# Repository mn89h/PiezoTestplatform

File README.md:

# Custom ASIC Test PCB for Ultrasonic Communication

This project involves the design and development of a custom printed circuit board (PCB) for testing an Application-Specific Integrated Circuit (ASIC) used in ultrasonic communication. The goal is to enable two-way ultrasonic communication with energy harvesting capabilities. This was developed as part of a project seminar in the Integrated Electronic Systems (IES) lab at the Technical University of Darmstadt.

Features:

    Ultrasonic Transmission and Reception: Supports two-way communication using piezoelectric transducers for transmitting and receiving ultrasonic waves.
    Custom PCB Design: Designed a custom PCB including components like a piezo driver, analog-to-digital converter (ADC), comparator, and FPGA for signal processing.
    Energy Harvesting: Capable of using wireless power harvesting techniques for communication where battery power is not feasible.
    FPGA Control: The system is controlled by a Xilinx Spartan-7 FPGA, with signal processing logic implemented in Verilog.

## System Overview

The system consists of both hardware and software platforms:

    Hardware: Includes a piezo driver stage, input amplifier, ADC, comparator, and FPGA. The PCB was designed using KiCAD 6.0.
    Software: Implemented in Verilog for the Xilinx Spartan-7 FPGA, handling communication, data transfer, and signal processing.

## Project Structure

    Piezo_DevBoard: A two-layer PCB designed for high-frequency ultrasonic communication with minimal noise and optimal power management.
    Piezo_TestPlatform: The FPGA core handles the communication between the FPGA and external systems through serial interfaces and processes data from the piezo transducers. Python code for interpreting incoming data is provided in the misc folder.

## Detailed Overview

Please refer to the [report](Report/main.pdf) and [presentation](Presentation/Präsentation.pdf) for a more in-depth look.

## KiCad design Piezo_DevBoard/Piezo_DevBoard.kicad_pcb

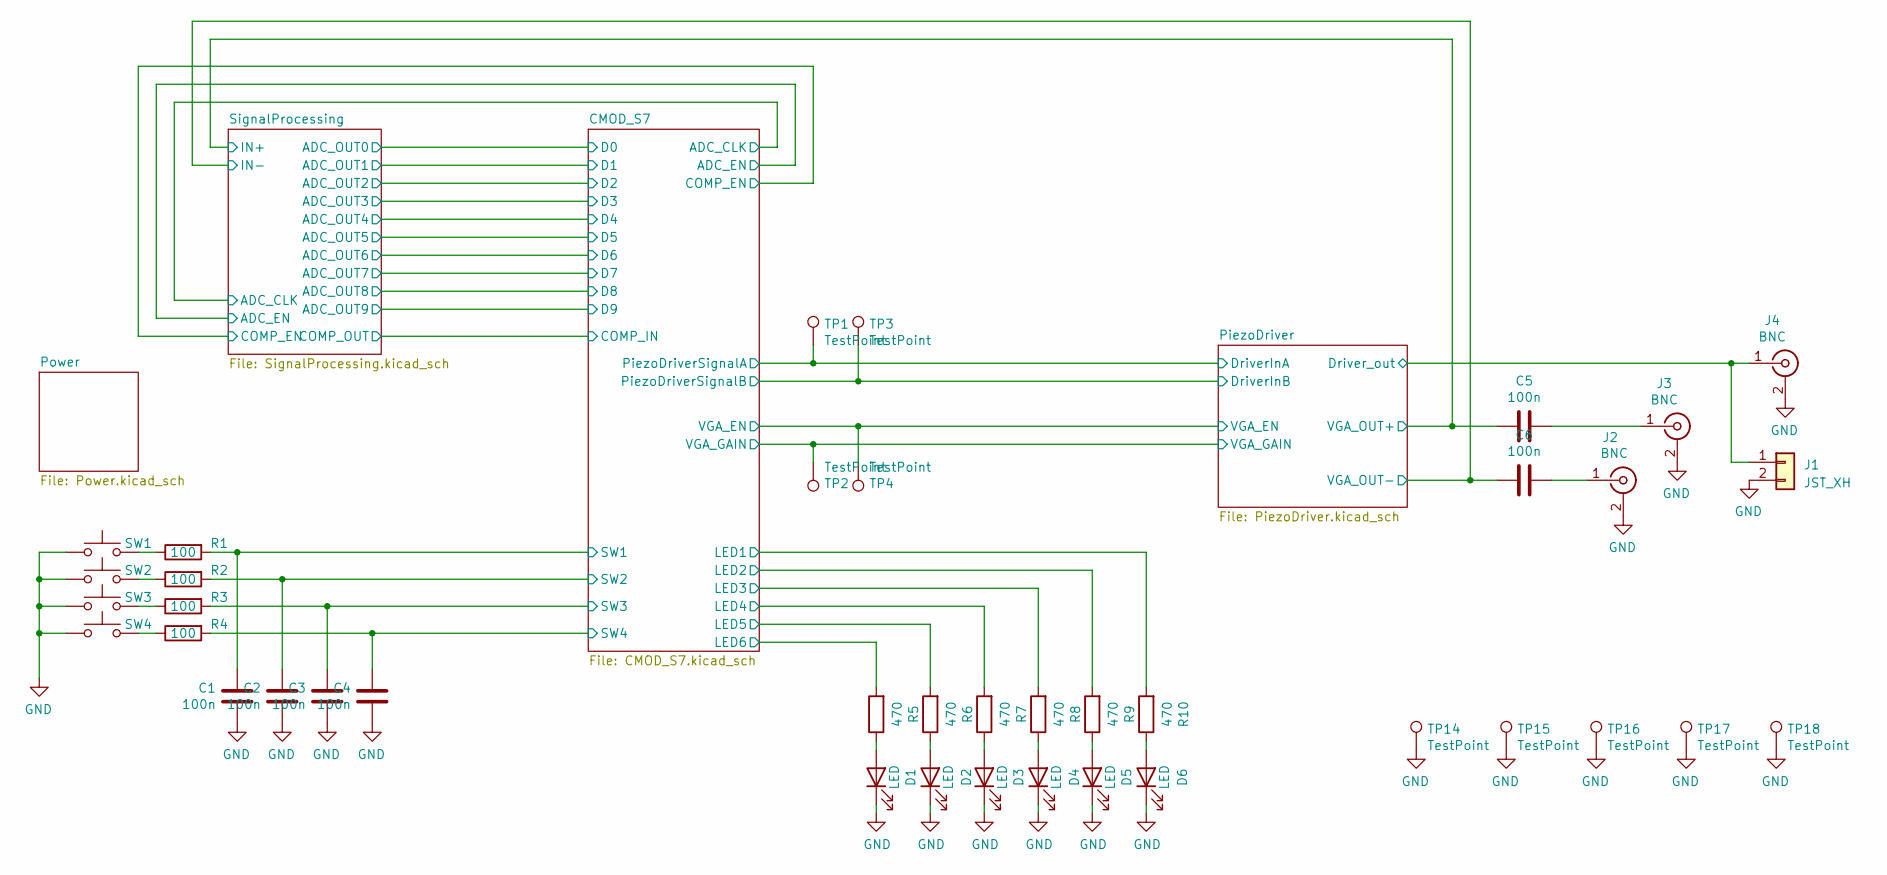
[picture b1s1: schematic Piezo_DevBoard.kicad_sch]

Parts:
C1, C2, C3, C4, C5, C6: 100n; C_0603_1608Metric_Pad1.08x0.95mm_HandSolder
D1, D2, D3, D4, D5, D6: LED; LED_0805_2012Metric_Pad1.15x1.40mm_HandSolder
J1: JST_XH; JST_XH_B2B-XH-A_1x02_P2.50mm_Vertical
J2, J3, J4: BNC; BNC_Amphenol_B6252HB-NPP3G-50_Horizontal
R1, R2, R3, R4: 100; R_0603_1608Metric_Pad0.98x0.95mm_HandSolder
R5, R6, R7, R8, R9, R10: 470; R_0603_1608Metric_Pad0.98x0.95mm_HandSolder
SW1, SW2, SW3, SW4: SW_Push; SW_Push_1P1T_NO_6x6mm_H9.5mm
TP1, TP2, TP3, TP4, TP14, TP15, TP16, TP17, TP18: TestPoint; TestPoint_Loop_D1.80mm_Drill1.0mm_Beaded

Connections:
/CMOD_S7/LED1: R10.2; also elsewhere on the board
/CMOD_S7/LED2: R9.2; also elsewhere on the board
/CMOD_S7/LED3: R8.2; also elsewhere on the board
/CMOD_S7/LED4: R7.2; also elsewhere on the board
/CMOD_S7/LED5: R6.2; also elsewhere on the board
/CMOD_S7/LED6: R5.2; also elsewhere on the board
/CMOD_S7/PiezoDriverSignalA: TP1.1; also elsewhere on the board
/CMOD_S7/PiezoDriverSignalB: TP3.1; also elsewhere on the board
/CMOD_S7/SW1: C1.1, R1.2; also elsewhere on the board
/CMOD_S7/SW2: C2.1, R2.2; also elsewhere on the board
/CMOD_S7/SW3: C3.1, R3.2; also elsewhere on the board
/CMOD_S7/SW4: C4.1, R4.2; also elsewhere on the board
/CMOD_S7/VGA_EN: TP4.1; also elsewhere on the board
/CMOD_S7/VGA_GAIN: TP2.1; also elsewhere on the board
/PiezoDriver/Driver_out: J1.1, J4.1 (In); also elsewhere on the board
/PiezoDriver/VGA_OUT+: C5.2; also elsewhere on the board
/PiezoDriver/VGA_OUT-: C6.2; also elsewhere on the board
GND: C1.2, C2.2, C3.2, C4.2, D1.1 (K), D2.1 (K), D3.1 (K), D4.1 (K), D5.1 (K), D6.1 (K), J1.2, J2.2 (Ext), J3.2 (Ext), J4.2 (Ext), SW1.2, SW2.2, SW3.2, SW4.2, TP14.1, TP15.1, TP16.1, TP17.1, TP18.1; also elsewhere on the board
unnamed: C5.1, J3.1 (In)
unnamed: C6.1, J2.1 (In)
unnamed: D1.2 (A), R5.1
unnamed: D2.2 (A), R6.1
unnamed: D3.2 (A), R7.1
unnamed: D4.2 (A), R8.1
unnamed: D5.2 (A), R9.1
unnamed: D6.2 (A), R10.1
unnamed: R1.1, SW1.1
unnamed: R2.1, SW2.1
unnamed: R3.1, SW3.1
unnamed: R4.1, SW4.1

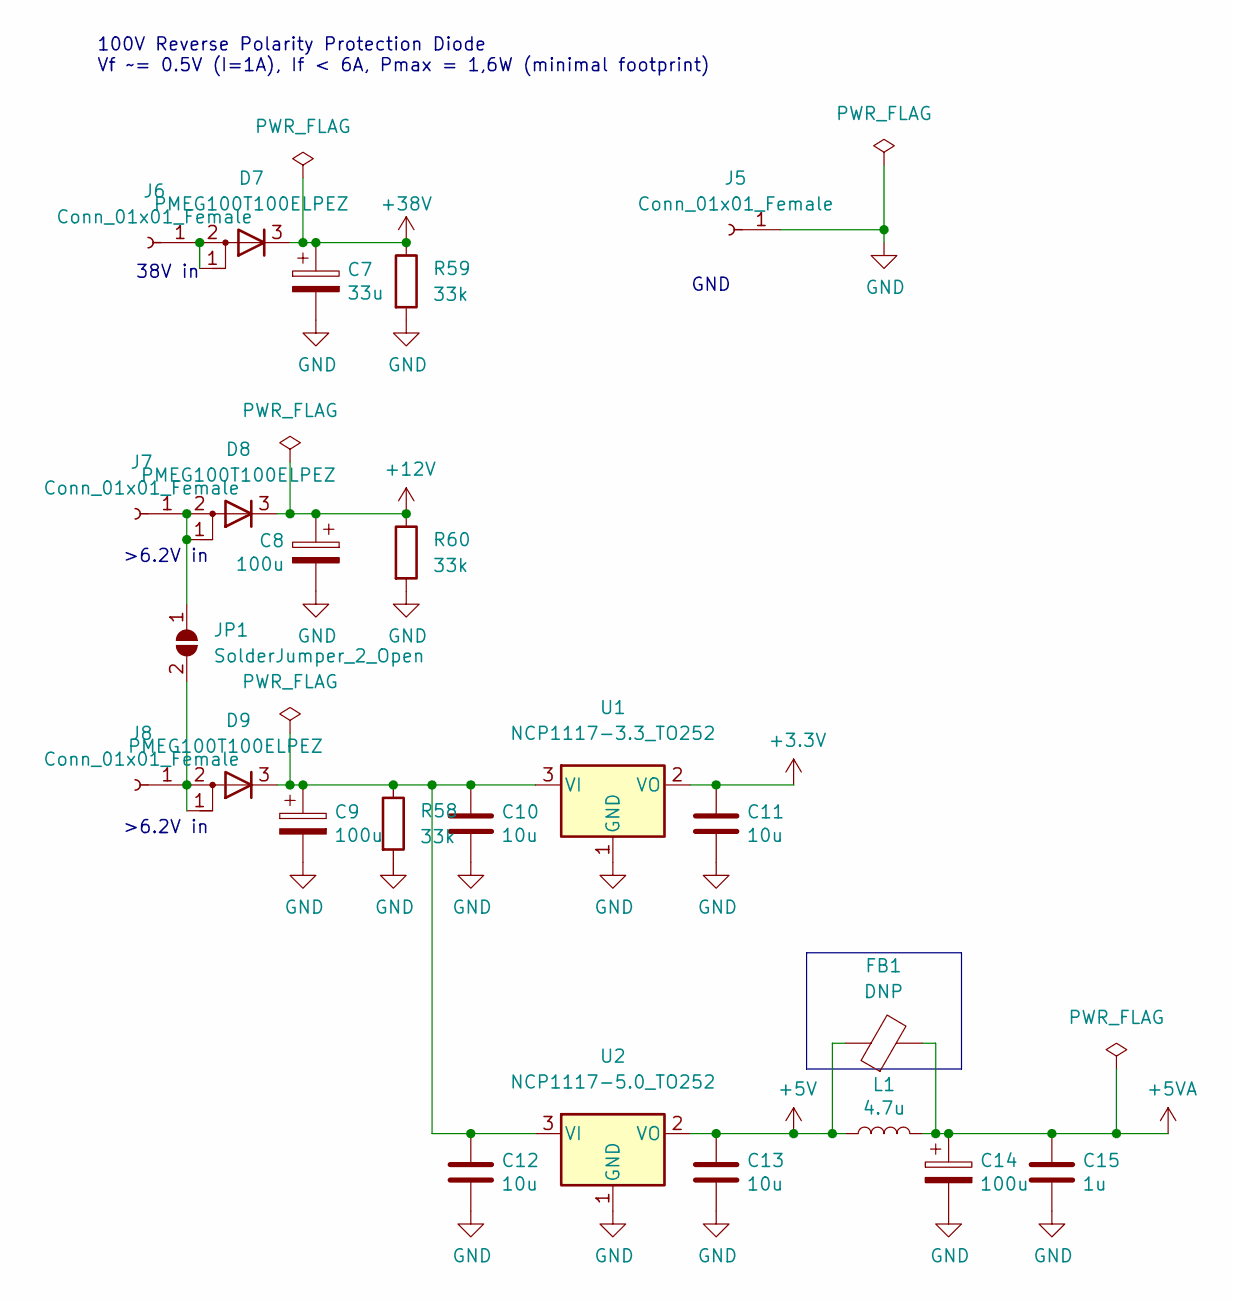
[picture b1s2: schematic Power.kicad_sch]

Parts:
C7: 33u; CP_Elec_10x10.5
C8, C9, C14: 100u; CP_Elec_6.3x7.7
C10, C11, C12, C13: 10u; C_0805_2012Metric_Pad1.18x1.45mm_HandSolder
C15: 1u; C_0603_1608Metric_Pad1.08x0.95mm_HandSolder
D7, D8, D9: PMEG100T100ELPEZ; Nexperia_CFP15_SOT-1289
FB1: DNP; L_0603_1608Metric_Pad1.05x0.95mm_HandSolder
J5, J6, J7, J8: Conn_01x01_Female; BananaJack_24.243
JP1: SolderJumper_2_Open; SolderJumper-2_P1.3mm_Open_TrianglePad1.0x1.5mm
L1: 4.7u; L_Wuerth_MAPI-4030
R58, R59, R60: 33k; R_1206_3216Metric_Pad1.30x1.75mm_HandSolder
U1: NCP1117-3.3_TO252; TO-252-2
U2: NCP1117-5.0_TO252; TO-252-2

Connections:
+3.3V: C11.1, U1.2 (VO); also elsewhere on the board
+5V: C13.1, FB1.1, L1.1, U2.2 (VO); also elsewhere on the board
+5VA: C14.1, C15.1, FB1.2, L1.2; also elsewhere on the board
+12V: C8.1, D8.3 (K), R60.1; also elsewhere on the board
+38V: C7.1, D7.3 (K), R59.1; also elsewhere on the board
GND: C7.2, C8.2, C9.2, C10.2, C11.2, C12.2, C13.2, C14.2, C15.2, J5.1, R58.2, R59.2, R60.2, U1.1 (GND), U2.1 (GND); also elsewhere on the board
unnamed: C9.1, C10.1, C12.1, D9.3 (K), R58.1, U1.3 (VI), U2.3 (VI)
unnamed: D7.1 (A), D7.2 (A), J6.1
unnamed: D8.1 (A), D8.2 (A), J7.1, JP1.1 (A)
unnamed: D9.1 (A), D9.2 (A), J8.1, JP1.2 (B)

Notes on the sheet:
38V in
>6.2V in
GND
100V Reverse Polarity Protection Diode Vf ~= 0.5V (I=1A), If < 6A, Pmax = 1,6W (minimal footprint)

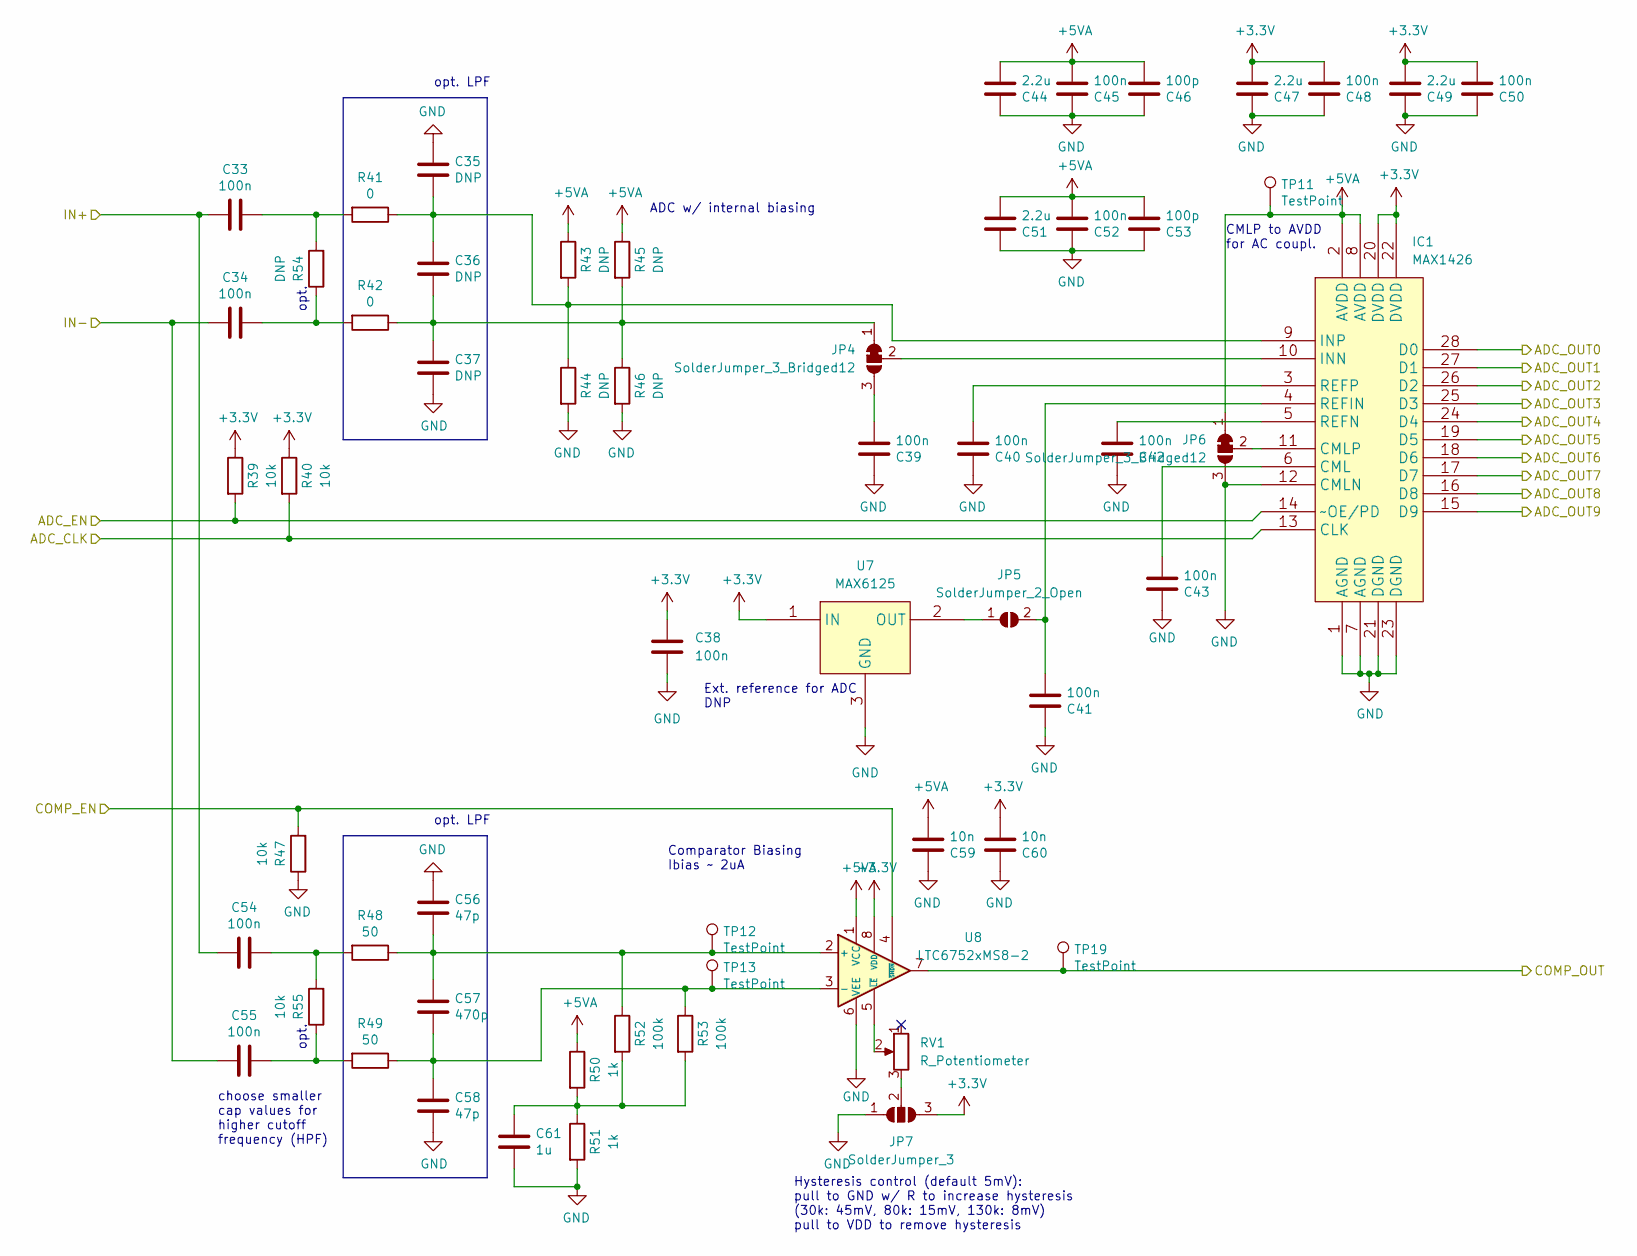
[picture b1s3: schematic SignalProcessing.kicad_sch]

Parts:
C33, C34, C38, C39, C40, C41, C42, C43, C45, C48, C50, C52, C54, C55: 100n; C_0603_1608Metric_Pad1.08x0.95mm_HandSolder
C35, C36, C37: DNP; C_0603_1608Metric_Pad1.08x0.95mm_HandSolder
C44, C47, C49, C51: 2.2u; C_0603_1608Metric_Pad1.08x0.95mm_HandSolder
C46, C53: 100p; C_0603_1608Metric_Pad1.08x0.95mm_HandSolder
C56, C58: 47p; C_0603_1608Metric_Pad1.08x0.95mm_HandSolder
C57: 470p; C_0603_1608Metric_Pad1.08x0.95mm_HandSolder
C59, C60: 10n; C_0603_1608Metric_Pad1.08x0.95mm_HandSolder
C61: 1u; C_0603_1608Metric_Pad1.08x0.95mm_HandSolder
IC1: MAX1426; SSOP-28_5.3x10.2mm_P0.65mm
JP4, JP6: SolderJumper_3_Bridged12; SolderJumper-3_P1.3mm_Bridged12_RoundedPad1.0x1.5mm
JP5: SolderJumper_2_Open; SolderJumper-2_P1.3mm_Open_RoundedPad1.0x1.5mm
JP7: SolderJumper_3; SolderJumper-3_P1.3mm_Open_RoundedPad1.0x1.5mm
R39, R40, R47, R55: 10k; R_0603_1608Metric_Pad0.98x0.95mm_HandSolder
R41, R42: 0; R_0603_1608Metric_Pad0.98x0.95mm_HandSolder
R43, R44, R45, R46, R54: DNP; R_0603_1608Metric_Pad0.98x0.95mm_HandSolder
R48, R49: 50; R_0603_1608Metric_Pad0.98x0.95mm_HandSolder
R50, R51: 1k; R_0603_1608Metric_Pad0.98x0.95mm_HandSolder
R52, R53: 100k; R_0603_1608Metric_Pad0.98x0.95mm_HandSolder
RV1: R_Potentiometer; Potentiometer_Bourns_3009P_Horizontal
TP11, TP12, TP13, TP19: TestPoint; TestPoint_Loop_D1.80mm_Drill1.0mm_Beaded
U7: MAX6125; SOT-23
U8: LTC6752xMS8-2; MSOP-8_3x3mm_P0.65mm

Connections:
+3.3V: C38.1, C47.2, C48.2, C49.2, C50.2, C60.2, IC1.20 (DVDD), IC1.22 (DVDD), JP7.3 (B), R39.1, R40.1, U7.1 (IN), U8.8 (VDD); also elsewhere on the board
+5VA: C44.2, C45.2, C46.2, C51.2, C52.2, C53.2, C59.2, IC1.2 (AVDD), IC1.8 (AVDD), JP6.1 (A), R43.1, R45.1, R50.1, TP11.1, U8.1 (VCC); also elsewhere on the board
/CMOD_S7/ADC_CLK: IC1.13 (CLK), R40.2; also elsewhere on the board
/CMOD_S7/ADC_EN: IC1.14 (~OE/PD), R39.2; also elsewhere on the board
/CMOD_S7/COMP_EN: R47.2, U8.4 (~SHDN); also elsewhere on the board
/CMOD_S7/COMP_IN: TP19.1, U8.7; also elsewhere on the board
/CMOD_S7/D0: IC1.28 (D0); also elsewhere on the board
/CMOD_S7/D1: IC1.27 (D1); also elsewhere on the board
/CMOD_S7/D2: IC1.26 (D2); also elsewhere on the board
/CMOD_S7/D3: IC1.25 (D3); also elsewhere on the board
/CMOD_S7/D4: IC1.24 (D4); also elsewhere on the board
/CMOD_S7/D5: IC1.19 (D5); also elsewhere on the board
/CMOD_S7/D6: IC1.18 (D6); also elsewhere on the board
/CMOD_S7/D7: IC1.17 (D7); also elsewhere on the board
/CMOD_S7/D8: IC1.16 (D8); also elsewhere on the board
/CMOD_S7/D9: IC1.15 (D9); also elsewhere on the board
/PiezoDriver/VGA_OUT+: C33.2, C54.2; also elsewhere on the board
/PiezoDriver/VGA_OUT-: C34.2, C55.2; also elsewhere on the board
GND: C35.1, C37.2, C38.2, C39.1, C40.1, C41.1, C42.1, C43.1, C44.1, C45.1, C46.1, C47.1, C48.1, C49.1, C50.1, C51.1, C52.1, C53.1, C56.1, C58.2, C59.1, C60.1, C61.2, IC1.1 (AGND), IC1.7 (AGND), IC1.12 (CMLN), IC1.21 (DGND), IC1.23 (DGND), JP6.3 (B), JP7.1 (A), R44.2, R46.2, R47.1, R51.2, U7.3 (GND), U8.6 (VEE); also elsewhere on the board
unnamed: C33.1, R41.2, R54.2
unnamed: C34.1, R42.2, R54.1
unnamed: C35.2, C36.1, IC1.9 (INP), R41.1, R43.2, R44.1
unnamed: C36.2, C37.1, JP4.1 (A), R42.1, R45.2, R46.1
unnamed: C39.2, JP4.3 (B)
unnamed: C40.2, IC1.3 (REFP)
unnamed: C41.2, IC1.4 (REFIN), JP5.2 (B)
unnamed: C42.2, IC1.5 (REFN)
unnamed: C43.2, IC1.6 (CML)
unnamed: C54.1, R48.2, R55.2
unnamed: C55.1, R49.2, R55.1
unnamed: C56.2, C57.1, R48.1, R52.1, TP12.1, U8.2 (+)
unnamed: C57.2, C58.1, R49.1, R53.1, TP13.1, U8.3 (-)
unnamed: C61.1, R50.2, R51.1, R52.2, R53.2
unnamed: IC1.10 (INN), JP4.2 (C)
unnamed: IC1.11 (CMLP), JP6.2 (C)
unnamed: JP5.1 (A), U7.2 (OUT)
unnamed: JP7.2 (C), RV1.3
unnamed: RV1.2, U8.5 (~LE)

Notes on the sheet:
opt. LPF
ADC w/ internal biasing
CMLP to AVDD for AC coupl.
opt.
Ext. reference for ADC DNP
Hysteresis control (default 5mV): pull to GND w/ R to increase hysteresis (30k: 45mV, 80k: 15mV, 130k: 8mV) pull to VDD to remove hysteresis
choose smaller cap values for higher cutoff frequency (HPF)
Comparator Biasing Ibias ~ 2uA

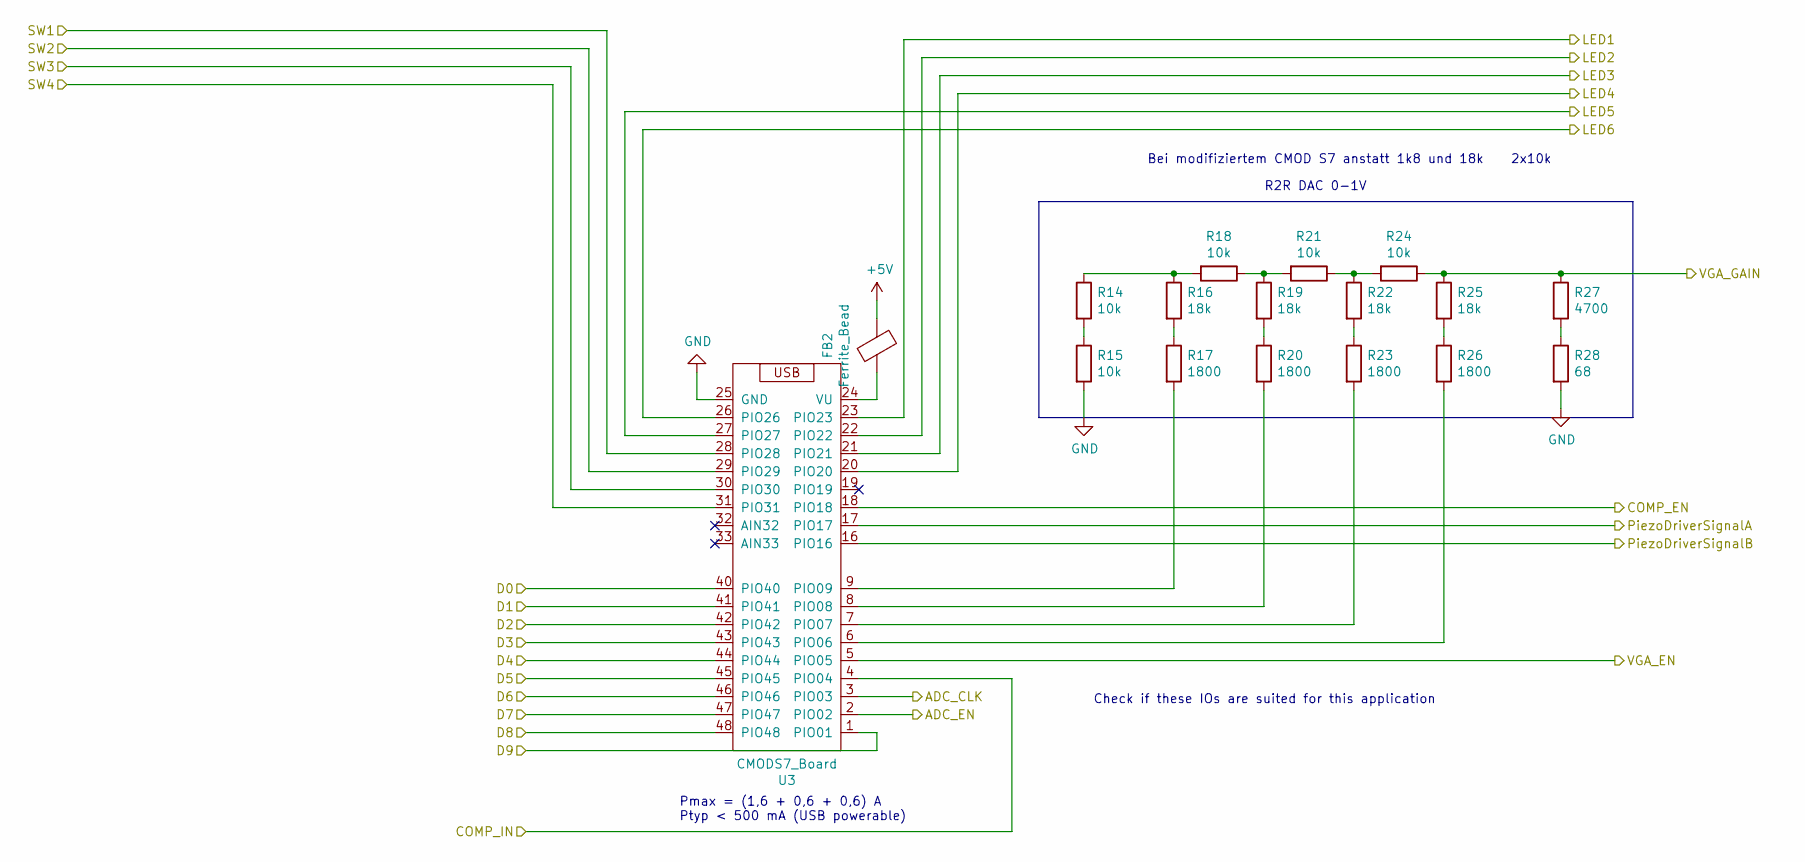
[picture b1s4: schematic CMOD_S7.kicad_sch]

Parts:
FB2: Ferrite_Bead; L_0603_1608Metric_Pad1.05x0.95mm_HandSolder
R14, R15, R18, R21, R24: 10k; R_0603_1608Metric_Pad0.98x0.95mm_HandSolder
R16, R19, R22, R25: 18k; R_0603_1608Metric_Pad0.98x0.95mm_HandSolder
R17, R20, R23, R26: 1800; R_0603_1608Metric_Pad0.98x0.95mm_HandSolder
R27: 4700; R_0603_1608Metric_Pad0.98x0.95mm_HandSolder
R28: 68; R_0603_1608Metric_Pad0.98x0.95mm_HandSolder
U3: CMODS7_Board; CMOD_S7_Socket

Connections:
+5V: FB2.2; also elsewhere on the board
/CMOD_S7/ADC_CLK: U3.3 (PIO03); also elsewhere on the board
/CMOD_S7/ADC_EN: U3.2 (PIO02); also elsewhere on the board
/CMOD_S7/COMP_EN: U3.18 (PIO18); also elsewhere on the board
/CMOD_S7/COMP_IN: U3.4 (PIO04); also elsewhere on the board
/CMOD_S7/D0: U3.40 (PIO40); also elsewhere on the board
/CMOD_S7/D1: U3.41 (PIO41); also elsewhere on the board
/CMOD_S7/D2: U3.42 (PIO42); also elsewhere on the board
/CMOD_S7/D3: U3.43 (PIO43); also elsewhere on the board
/CMOD_S7/D4: U3.44 (PIO44); also elsewhere on the board
/CMOD_S7/D5: U3.45 (PIO45); also elsewhere on the board
/CMOD_S7/D6: U3.46 (PIO46); also elsewhere on the board
/CMOD_S7/D7: U3.47 (PIO47); also elsewhere on the board
/CMOD_S7/D8: U3.48 (PIO48); also elsewhere on the board
/CMOD_S7/D9: U3.1 (PIO01); also elsewhere on the board
/CMOD_S7/LED1: U3.23 (PIO23); also elsewhere on the board
/CMOD_S7/LED2: U3.22 (PIO22); also elsewhere on the board
/CMOD_S7/LED3: U3.21 (PIO21); also elsewhere on the board
/CMOD_S7/LED4: U3.20 (PIO20); also elsewhere on the board
/CMOD_S7/LED5: U3.27 (PIO27); also elsewhere on the board
/CMOD_S7/LED6: U3.26 (PIO26); also elsewhere on the board
/CMOD_S7/PiezoDriverSignalA: U3.17 (PIO17); also elsewhere on the board
/CMOD_S7/PiezoDriverSignalB: U3.16 (PIO16); also elsewhere on the board
/CMOD_S7/SW1: U3.28 (PIO28); also elsewhere on the board
/CMOD_S7/SW2: U3.29 (PIO29); also elsewhere on the board
/CMOD_S7/SW3: U3.30 (PIO30); also elsewhere on the board
/CMOD_S7/SW4: U3.31 (PIO31); also elsewhere on the board
/CMOD_S7/VGA_EN: U3.5 (PIO05); also elsewhere on the board
/CMOD_S7/VGA_GAIN: R24.1, R25.1, R27.1; also elsewhere on the board
GND: R15.2, R28.2, U3.25 (GND); also elsewhere on the board
unnamed: FB2.1, U3.24 (VU)
unnamed: R14.1, R16.1, R18.2
unnamed: R14.2, R15.1
unnamed: R16.2, R17.1
unnamed: R17.2, U3.9 (PIO09)
unnamed: R18.1, R19.1, R21.2
unnamed: R19.2, R20.1
unnamed: R20.2, U3.8 (PIO08)
unnamed: R21.1, R22.1, R24.2
unnamed: R22.2, R23.1
unnamed: R23.2, U3.7 (PIO07)
unnamed: R25.2, R26.1
unnamed: R26.2, U3.6 (PIO06)
unnamed: R27.2, R28.1

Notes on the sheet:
Pmax = (1,6 + 0,6 + 0,6) A Ptyp < 500 mA (USB powerable)
R2R DAC 0-1V
Check if these IOs are suited for this application
Bei modifiziertem CMOD S7 anstatt 1k8 und 18k 2x10k

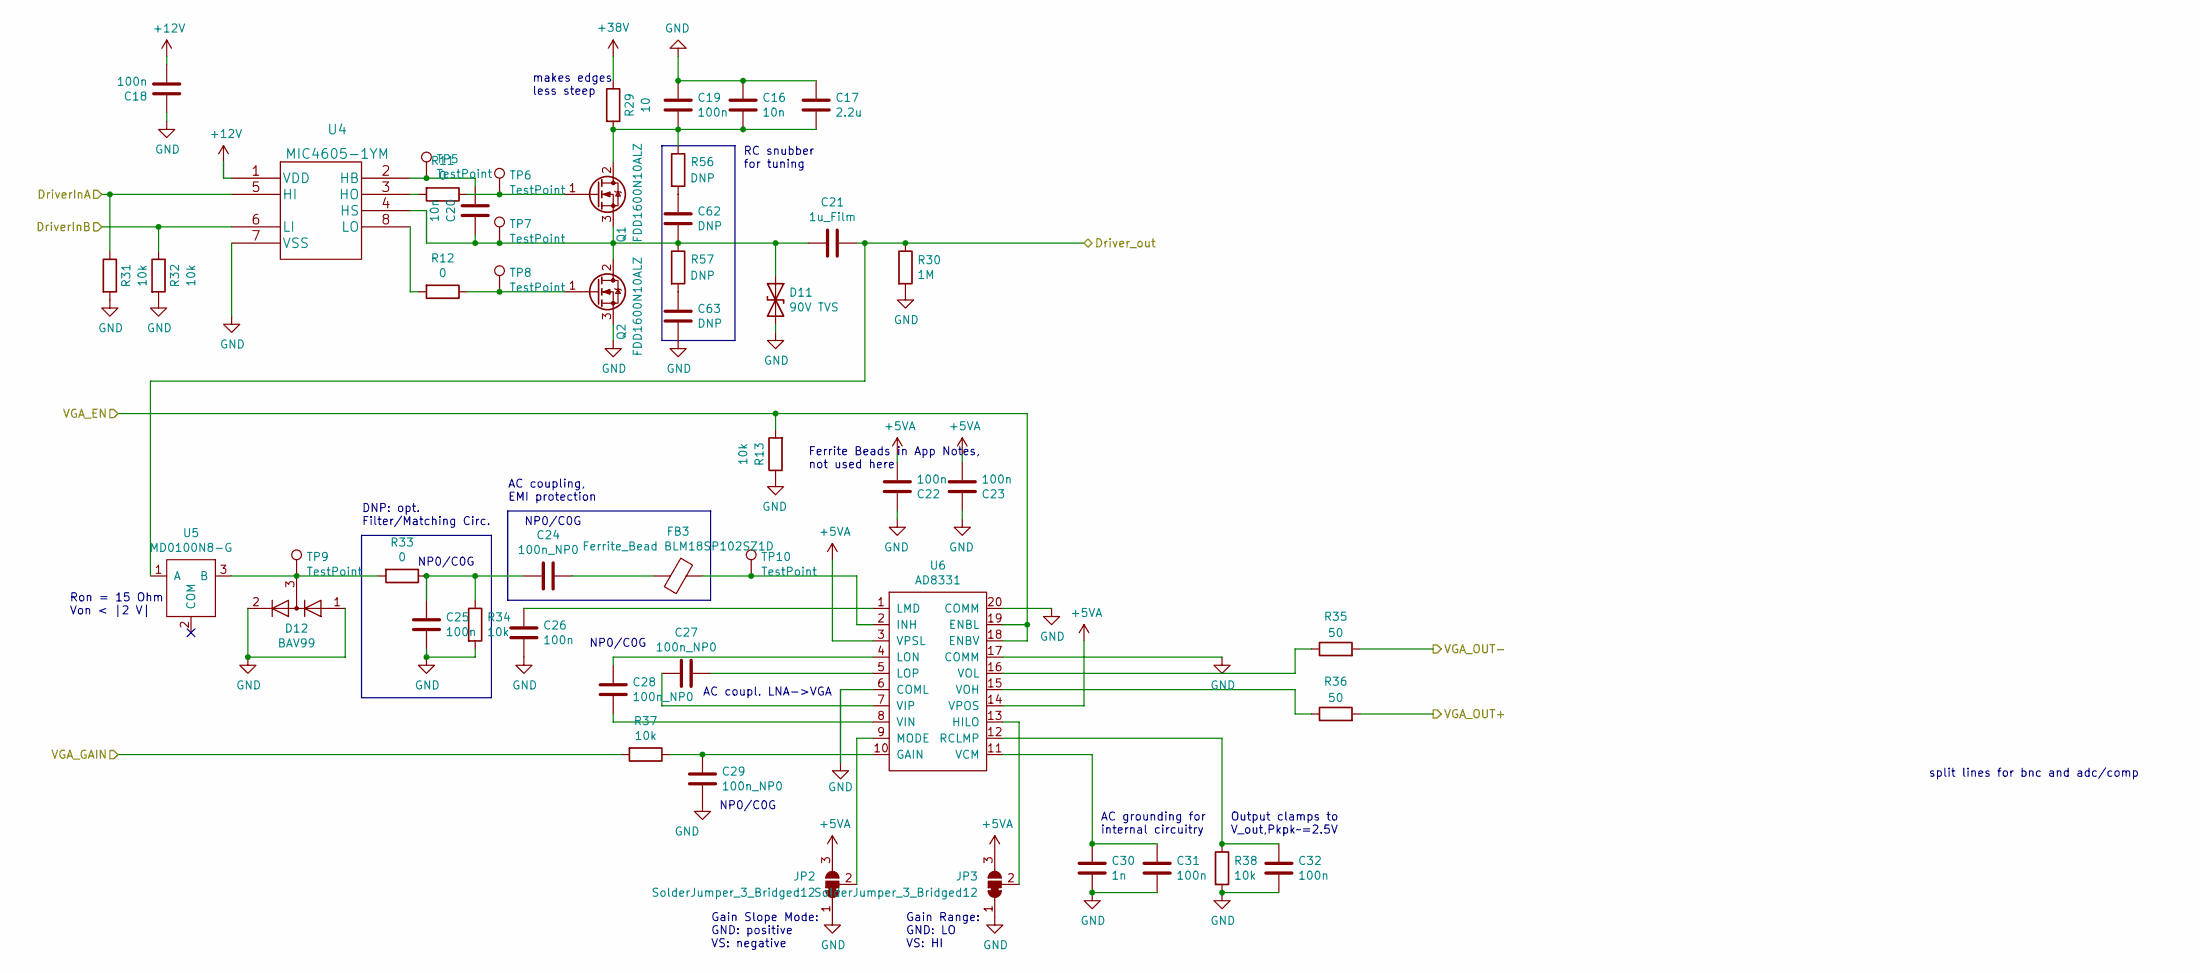
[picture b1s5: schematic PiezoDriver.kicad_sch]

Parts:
C16, C20: 10n; C_0603_1608Metric_Pad1.08x0.95mm_HandSolder
C17: 2.2u; C_1206_3216Metric_Pad1.33x1.80mm_HandSolder
C18, C19, C22, C23, C25, C26, C31, C32: 100n; C_0603_1608Metric_Pad1.08x0.95mm_HandSolder
C21: 1u_Film; C_2824_7260Metric_HandSolder
C24, C27, C28, C29: 100n_NP0; C_1206_3216Metric_Pad1.33x1.80mm_HandSolder
C30: 1n; C_0603_1608Metric_Pad1.08x0.95mm_HandSolder
C62, C63: DNP; C_0603_1608Metric_Pad1.08x0.95mm_HandSolder
D11: 90V TVS; D_SMA_Handsoldering
D12: BAV99; SOT-23
FB3: Ferrite_Bead BLM18SP102SZ1D; L_0603_1608Metric_Pad1.05x0.95mm_HandSolder
JP2, JP3: SolderJumper_3_Bridged12; SolderJumper-3_P1.3mm_Bridged12_RoundedPad1.0x1.5mm
Q1, Q2: FDD1600N10ALZ; TO-252-2
R11, R12, R33: 0; R_0603_1608Metric_Pad0.98x0.95mm_HandSolder
R13, R31, R32, R34, R37, R38: 10k; R_0603_1608Metric_Pad0.98x0.95mm_HandSolder
R29: 10; R_0603_1608Metric_Pad0.98x0.95mm_HandSolder
R30: 1M; R_0603_1608Metric_Pad0.98x0.95mm_HandSolder
R35, R36: 50; R_0603_1608Metric_Pad0.98x0.95mm_HandSolder
R56, R57: DNP; R_0603_1608Metric_Pad0.98x0.95mm_HandSolder
TP5, TP6, TP7, TP8, TP9, TP10: TestPoint; TestPoint_Loop_D1.80mm_Drill1.0mm_Beaded
U4: MIC4605-1YM; SOIC-8_3.9x4.9mm_P1.27mm
U5: MD0100N8-G; SOT-89-3_Handsoldering
U6: AD8331; QSOP-20_3.9x8.7mm_P0.635mm

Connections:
+5VA: C22.2, C23.2, JP2.3 (B), JP3.3 (B), U6.3 (VPSL), U6.14 (VPOS); also elsewhere on the board
+12V: C18.2, U4.1 (VDD); also elsewhere on the board
+38V: R29.1; also elsewhere on the board
/CMOD_S7/PiezoDriverSignalA: R31.1, U4.5 (HI); also elsewhere on the board
/CMOD_S7/PiezoDriverSignalB: R32.1, U4.6 (LI); also elsewhere on the board
/CMOD_S7/VGA_EN: R13.2, U6.18 (ENBV), U6.19 (ENBL); also elsewhere on the board
/CMOD_S7/VGA_GAIN: R37.2; also elsewhere on the board
/PiezoDriver/Driver_out: C21.1, R30.1, U5.1 (A); also elsewhere on the board
/PiezoDriver/VGA_OUT+: R36.2; also elsewhere on the board
/PiezoDriver/VGA_OUT-: R35.2; also elsewhere on the board
GND: C16.1, C17.1, C18.1, C19.1, C22.1, C23.1, C25.2, C26.2, C29.2, C30.2, C31.2, C32.2, C63.2, D11.2 (A2), D12.1 (K), D12.2 (A), JP2.1 (A), JP3.1 (A), Q2.3 (S), R13.1, R30.2, R31.2, R32.2, R34.2, R38.2, U4.7 (VSS), U6.6 (COML), U6.17 (COMM), U6.20 (COMM); also elsewhere on the board
unnamed: C16.2, C17.2, C19.2, Q1.2 (D), R29.2, R56.1
unnamed: C20.1, C21.2, C62.2, D11.1 (A1), Q1.3 (S), Q2.2 (D), R57.1, TP7.1, U4.4 (HS)
unnamed: C20.2, TP5.1, U4.2 (HB)
unnamed: C24.1, FB3.2
unnamed: C24.2, C25.1, R33.1, R34.1
unnamed: C26.1, U6.1 (LMD)
unnamed: C27.1, U6.5 (LOP)
unnamed: C27.2, U6.7 (VIP)
unnamed: C28.1, U6.8 (VIN)
unnamed: C28.2, U6.4 (LON)
unnamed: C29.1, R37.1, U6.10 (GAIN)
unnamed: C30.1, C31.1, U6.11 (VCM)
unnamed: C32.1, R38.1, U6.12 (RCLMP)
unnamed: C62.1, R56.2
unnamed: C63.1, R57.2
unnamed: D12.3 (K), R33.2, TP9.1, U5.3 (B)
unnamed: FB3.1, TP10.1, U6.2 (INH)
unnamed: JP2.2 (C), U6.9 (MODE)
unnamed: JP3.2 (C), U6.13 (HILO)
unnamed: Q1.1 (G), R11.1, TP6.1
unnamed: Q2.1 (G), R12.1, TP8.1
unnamed: R11.2, U4.3 (HO)
unnamed: R12.2, U4.8 (LO)
unnamed: R35.1, U6.16 (VOL)
unnamed: R36.1, U6.15 (VOH)

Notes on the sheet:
makes edges less steep
NP0/C0G
Ron = 15 Ohm Von < |2 V|
AC grounding for internal circuitry
AC coupling, EMI protection
split lines for bnc and adc/comp
Output clamps to V_out,Pkpk~=2.5V
Gain Slope Mode: GND: positive VS: negative
Gain Range: GND: LO VS: HI
AC coupl. LNA->VGA
RC snubber for tuning
DNP: opt. Filter/Matching Circ.
Ferrite Beads in App Notes, not used here

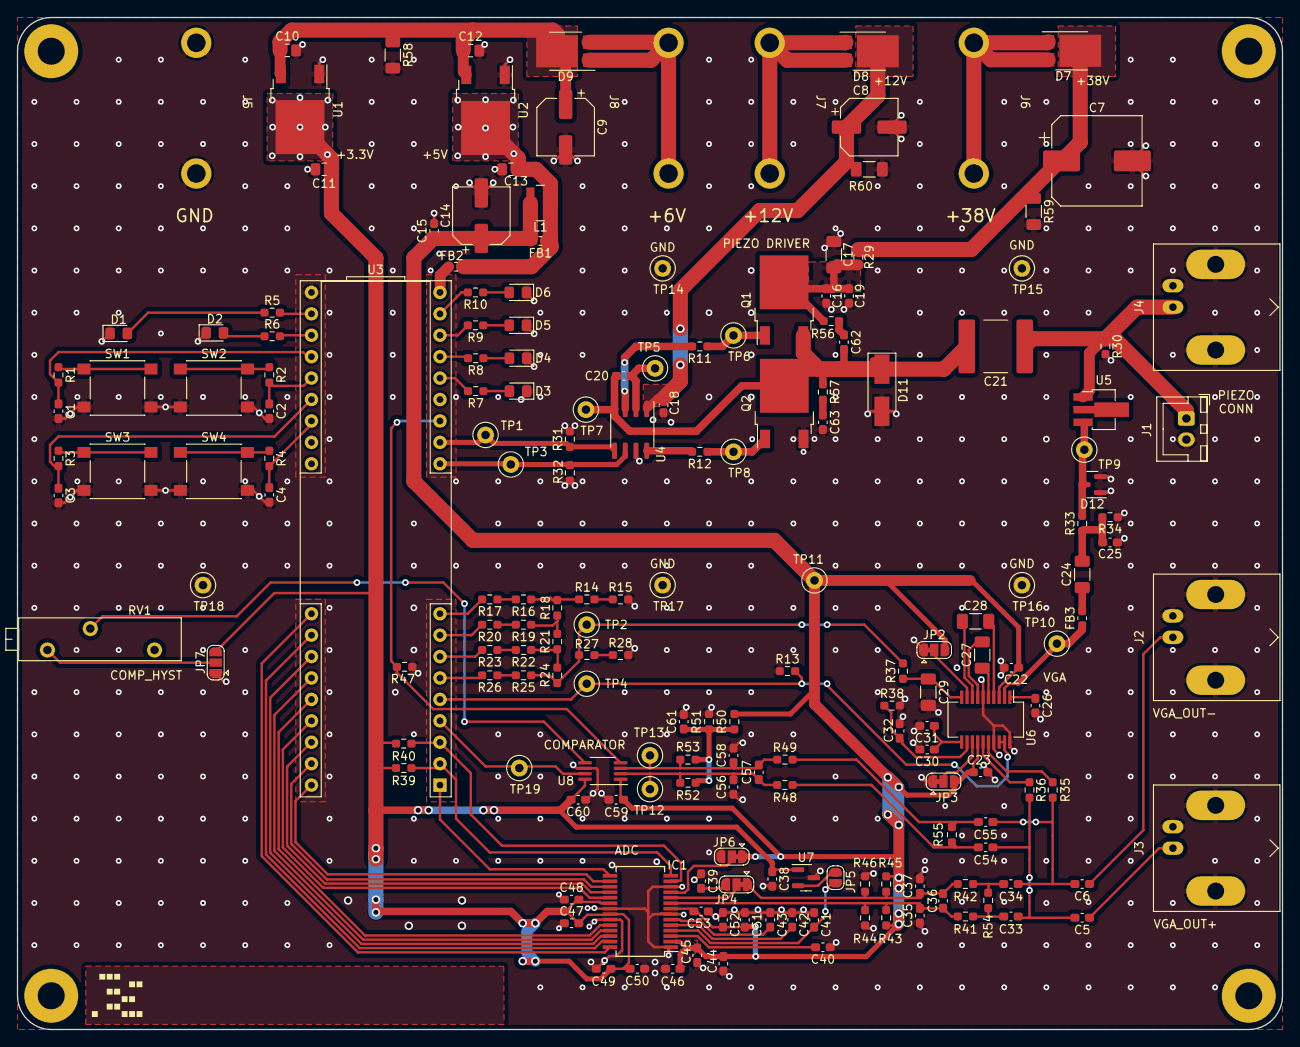
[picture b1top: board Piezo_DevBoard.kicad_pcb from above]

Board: 2 copper layers, 150.0 x 120.0 mm, 188 parts (0 on the bottom side), 111 nets.

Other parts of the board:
J1001: eurocard_extended

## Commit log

2021-06-16 Replace C:\Users\Timo\Piezo_Board.zip
2021-06-21 initial release
2021-06-21 add gitignore
2021-06-25 Piezo_Driver Implemented
2021-06-30 Piezo Comm. Protocol Implemented
2021-08-12 Backup
2021-11-26 added Serial Communication
2023-02-17 testplatform bringup for new devboard (REV1 01/23)
2023-02-28 comm_protocol rx_handler bugfix (missing command interpretation in serial_rx_handler.v) other minor improvements
2023-03-01 comm_protocol: added command feedback
2023-03-22 uart_tx update: remove unnecessary 2nd fin cycle
2023-03-22 include stress test state in comm_protocol
2023-03-22 add initial adc_driver (not ready for shipping): - working width and frequency reconfiguration - simulation adjustments, does not use real input - resets and cdc not final
2023-03-22 adc_driver: serial tx fixes removed legacy code
2023-03-25 adc_driver update: - command fixes - optional simulation command - adc stream head and tail
2023-03-25 adc data stream interpreter
2023-03-25 update clk generation and constraints
2023-03-30 log_interpreter: multiple data frames/sources adc_driver: adapted for better logging and minor cleanups in drp
2023-04-19 fifo_aggregate fix: ensure full set only one cycle
2023-04-19 comp_driver: initial push, working
2023-05-19 update adc_driver and vga_driver, piezo_driver bringup
2023-05-19 comm_protocol and piezo_driver update: - adjustable frequency divider - better serial communication
2023-05-19 updated Vivado Project settings
2023-05-19 update constraints
2023-05-19 added README
2023-06-22 fifo_aggregate: fix counter reg size fixes wrong shift amount for input width >8
2023-06-22 adc_driver: add additional simulation triggering
2023-06-23 comp_driver: remove adjustable frequency now set to 25MHz fixed. Changed fifo input width to avoid overflows.
2023-06-28 changed UART baudrate to 2.4M (max value)
2023-06-28 added testbenches
2023-06-28 constraints: add reset false path
2023-06-30 repo cleanup
2023-06-30 DevBoard: KiCad files
2023-08-15 optimizations and cleanup
2023-08-16 schematic update rev3 RC snubber, discharge resistors, updated footprint sizes, NMOS fixed
2023-08-16 memory configuration files based on latest version
2023-08-16 adjust default cock divider
2023-08-17 added simulation files and real-world testing results
2023-09-30 added report and presentation
